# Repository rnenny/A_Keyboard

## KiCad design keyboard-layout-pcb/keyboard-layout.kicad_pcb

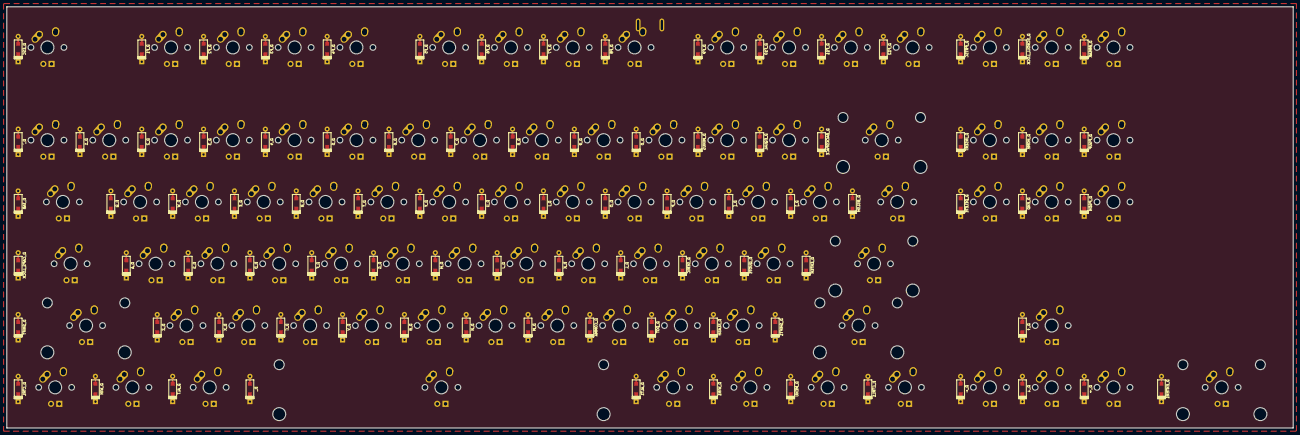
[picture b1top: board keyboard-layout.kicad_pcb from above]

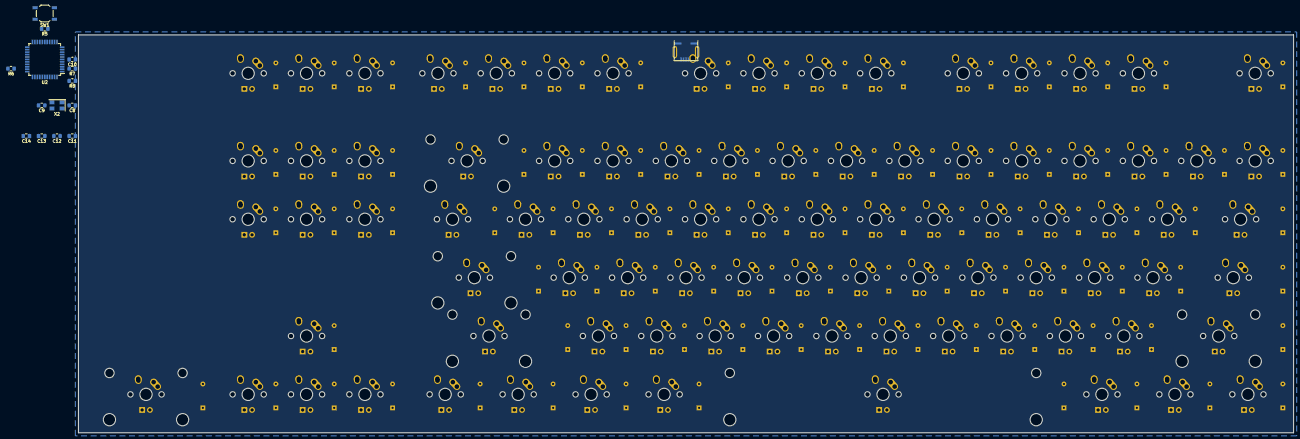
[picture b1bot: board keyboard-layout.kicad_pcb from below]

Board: 2 copper layers, 396.5 x 129.8 mm, 191 parts (15 on the bottom side), 116 nets, no tracks yet.

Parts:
C8, C9, C10, C11, C12, C13, C14: 22pF; C_0805_2012Metric_Pad1.15x1.40mm_HandSolder
D_, D_0, D_1, D_2, D_3, D_4, D_5, D_6, D_7, D_8, D_9: D; D_SOD123_axial
D_A: D; D_SOD123_axial
D_ALT, D_ALT1: D; D_SOD123_axial
D_B: D; D_SOD123_axial
D_BACKSPACE: D; D_SOD123_axial
D_BREAK: D; D_SOD123_axial
D_BSLSH: D; D_SOD123_axial
D_C: D; D_SOD123_axial
D_CAPS_LOCK: D; D_SOD123_axial
D_COMMA: D; D_SOD123_axial
D_CTRL, D_CTRL1: D; D_SOD123_axial
D_D: D; D_SOD123_axial
D_DELETE: D; D_SOD123_axial
D_DOT: D; D_SOD123_axial
D_E: D; D_SOD123_axial
D_END: D; D_SOD123_axial
D_ENTER, D_ENTER1: D; D_SOD123_axial
D_EQUAL: D; D_SOD123_axial
D_ESC: D; D_SOD123_axial
D_F, D_F1, D_F2, D_F3, D_F4, D_F5, D_F6, D_F7, D_F8, D_F9, D_F10, D_F11, D_F12: D; D_SOD123_axial
D_G: D; D_SOD123_axial
D_H: D; D_SOD123_axial
D_HOME: D; D_SOD123_axial
D_I: D; D_SOD123_axial
D_INSERT: D; D_SOD123_axial
D_J: D; D_SOD123_axial
D_K: D; D_SOD123_axial
D_L: D; D_SOD123_axial
D_M: D; D_SOD123_axial
D_MENU: D; D_SOD123_axial
D_MINUS: D; D_SOD123_axial
D_N: D; D_SOD123_axial
D_O: D; D_SOD123_axial
D_P: D; D_SOD123_axial
D_PGDN: D; D_SOD123_axial
D_PGUP: D; D_SOD123_axial
D_PRTSC: D; D_SOD123_axial
D_Q: D; D_SOD123_axial
D_QUOTE: D; D_SOD123_axial
D_R: D; D_SOD123_axial
D_S: D; D_SOD123_axial
D_SCROLL_LOCK: D; D_SOD123_axial
D_SEMIC: D; D_SOD123_axial
D_SHIFT, D_SHIFT1: D; D_SOD123_axial
D_SLASH: D; D_SOD123_axial
D_T: D; D_SOD123_axial
D_TAB: D; D_SOD123_axial
D_U: D; D_SOD123_axial
D_V: D; D_SOD123_axial
D_W: D; D_SOD123_axial
D_WIN, D_WIN1: D; D_SOD123_axial
D_X: D; D_SOD123_axial
D_Y: D; D_SOD123_axial
D_Z: D; D_SOD123_axial
D_[: D; D_SOD123_axial
D_]: D; D_SOD123_axial
D_`: D; D_SOD123_axial
D_←: D; D_SOD123_axial
D_↑: D; D_SOD123_axial
D_→: D; D_SOD123_axial
D_↓: D; D_SOD123_axial
K_: KEYSW; MX-6.25U-NoLED
K_0, K_1, K_2, K_3, K_4, K_5, K_6, K_7, K_8, K_9: KEYSW; MX-1U-NoLED
K_A: KEYSW; MX-1U-NoLED
K_ALT, K_ALT1: KEYSW; MX-1.25U-NoLED
K_B: KEYSW; MX-1U-NoLED
K_BACKSPACE: KEYSW; MX-2U-NoLED
K_BREAK: KEYSW; MX-1U-NoLED
K_BSLSH: KEYSW; MX-1.5U-NoLED
K_C: KEYSW; MX-1U-NoLED
K_CAPS_LOCK: KEYSW; MX-1.75U-NoLED
K_COMMA: KEYSW; MX-1U-NoLED
K_CTRL, K_CTRL1: KEYSW; MX-1.25U-NoLED
K_D: KEYSW; MX-1U-NoLED
K_DELETE: KEYSW; MX-1U-NoLED
K_DOT: KEYSW; MX-1U-NoLED
K_E: KEYSW; MX-1U-NoLED
K_END: KEYSW; MX-1U-NoLED
K_ENTER: KEYSW; MX-2.25U-NoLED
K_ENTER1: KEYSW; MX-2U-NoLED
K_EQUAL: KEYSW; MX-1U-NoLED
K_ESC: KEYSW; MX-1U-NoLED
K_F, K_F1, K_F2, K_F3, K_F4, K_F5, K_F6, K_F7, K_F8, K_F9, K_F10, K_F11, K_F12: KEYSW; MX-1U-NoLED
K_G: KEYSW; MX-1U-NoLED
K_H: KEYSW; MX-1U-NoLED
K_HOME: KEYSW; MX-1U-NoLED
K_I: KEYSW; MX-1U-NoLED
K_INSERT: KEYSW; MX-1U-NoLED
K_J: KEYSW; MX-1U-NoLED
K_K: KEYSW; MX-1U-NoLED
K_L: KEYSW; MX-1U-NoLED
K_M: KEYSW; MX-1U-NoLED
K_MENU: KEYSW; MX-1.25U-NoLED
K_MINUS: KEYSW; MX-1U-NoLED
K_N: KEYSW; MX-1U-NoLED
K_O: KEYSW; MX-1U-NoLED
K_P: KEYSW; MX-1U-NoLED
K_PGDN: KEYSW; MX-1U-NoLED
K_PGUP: KEYSW; MX-1U-NoLED
K_PRTSC: KEYSW; MX-1U-NoLED
K_Q: KEYSW; MX-1U-NoLED
K_QUOTE: KEYSW; MX-1U-NoLED
K_R: KEYSW; MX-1U-NoLED
K_S: KEYSW; MX-1U-NoLED
K_SCROLL_LOCK: KEYSW; MX-1U-NoLED
K_SEMIC: KEYSW; MX-1U-NoLED
K_SHIFT: KEYSW; MX-2.25U-NoLED
K_SHIFT1: KEYSW; MX-2.75U-NoLED
K_SLASH: KEYSW; MX-1U-NoLED
K_T: KEYSW; MX-1U-NoLED
K_TAB: KEYSW; MX-1.5U-NoLED
K_U: KEYSW; MX-1U-NoLED
K_V: KEYSW; MX-1U-NoLED
K_W: KEYSW; MX-1U-NoLED
K_WIN, K_WIN1: KEYSW; MX-1.25U-NoLED
K_X: KEYSW; MX-1U-NoLED
K_Y: KEYSW; MX-1U-NoLED
K_Z: KEYSW; MX-1U-NoLED
K_[: KEYSW; MX-1U-NoLED
K_]: KEYSW; MX-1U-NoLED
K_`: KEYSW; MX-1U-NoLED
K_←: KEYSW; MX-1U-NoLED
K_↑: KEYSW; MX-1U-NoLED
K_→: KEYSW; MX-1U-NoLED
K_↓: KEYSW; MX-1U-NoLED
R5, R6: 10k; R_0805_2012Metric_Pad1.15x1.40mm_HandSolder
R7, R8: 22u; R_0805_2012Metric_Pad1.15x1.40mm_HandSolder
SW1: SW_PUSH; SW_SPST_TL3342
U2: ATMEGA32U4; TQFP-44_10x10mm_P0.8mm
USB2: USB_mini_micro_B; USB_miniB_hirose_5S8
X2: XTAL_GND; Crystal_SMD_5032-4Pin_5.0x3.2mm

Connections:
/col0: D_CAPS_LOCK.1, D_CTRL.1, D_ESC.1, D_SHIFT.1, D_TAB.1, D_`.1, U2.32
/col1: D_1.1, D_A.1, D_F1.1, D_Q.1, D_WIN.1, D_Z.1, U2.31
/col2: D_2.1, D_ALT.1, D_F2.1, D_S.1, D_W.1, D_X.1, U2.12
/col3: D_.1, D_3.1, D_C.1, D_D.1, D_E.1, D_F3.1, U2.30
/col4: D_4.1, D_ALT1.1, D_F.1, D_F4.1, D_R.1, D_V.1, U2.29
/col5: D_5.1, D_B.1, D_F5.1, D_G.1, D_T.1, D_WIN1.1, U2.28
/col6: D_6.1, D_F6.1, D_H.1, D_MENU.1, D_N.1, D_Y.1, U2.11
/col7: D_7.1, D_CTRL1.1, D_F7.1, D_J.1, D_M.1, D_U.1, U2.10
/col8: D_8.1, D_COMMA.1, D_F8.1, D_I.1, D_K.1, D_←.1, U2.9
/col9: D_9.1, D_DOT.1, D_F9.1, D_L.1, D_O.1, D_↓.1, U2.8
/col10: D_0.1, D_F10.1, D_P.1, D_SEMIC.1, D_SLASH.1, D_→.1, U2.37
/col11: D_ENTER1.1, D_F11.1, D_MINUS.1, D_QUOTE.1, D_SHIFT1.1, D_[.1, U2.38
/col12: D_ENTER.1, D_EQUAL.1, D_F12.1, D_].1, D_↑.1, U2.39
/col13: D_BACKSPACE.1, D_BSLSH.1, D_PRTSC.1, U2.40
/col14: D_DELETE.1, D_INSERT.1, D_SCROLL_LOCK.1, U2.41
/col15: D_BREAK.1, D_END.1, D_HOME.1
/col16: D_PGDN.1, D_PGUP.1
GND: C8.2, C9.2, C10.2, C11.2, C12.2, C13.2, C14.2, R6.2, SW1.1, U2.5, U2.15, U2.23, USB2.5, USB2.6, X2.3
unnamed: C8.1, U2.16
unnamed: C9.1, U2.17
unnamed: C10.1, U2.6
unnamed: D_0.2, K_0.2
unnamed: D_1.2, K_1.2
unnamed: D_2.2, K_2.2
unnamed: D_3.2, K_3.2
unnamed: D_4.2, K_4.2
unnamed: D_5.2, K_5.2
unnamed: D_6.2, K_6.2
unnamed: D_7.2, K_7.2
unnamed: D_8.2, K_8.2
unnamed: D_9.2, K_9.2
unnamed: D_.2, K_.2
unnamed: D_A.2, K_A.2
unnamed: D_ALT1.2, K_ALT1.2
unnamed: D_ALT.2, K_ALT.2
unnamed: D_B.2, K_B.2
unnamed: D_BACKSPACE.2, K_BACKSPACE.2
unnamed: D_BREAK.2, K_BREAK.2
unnamed: D_BSLSH.2, K_BSLSH.2
unnamed: D_C.2, K_C.2
unnamed: D_CAPS_LOCK.2, K_CAPS_LOCK.2
unnamed: D_COMMA.2, K_COMMA.2
unnamed: D_CTRL1.2, K_CTRL1.2
unnamed: D_CTRL.2, K_CTRL.2
unnamed: D_D.2, K_D.2
unnamed: D_DELETE.2, K_DELETE.2
unnamed: D_DOT.2, K_DOT.2
unnamed: D_E.2, K_E.2
unnamed: D_END.2, K_END.2
unnamed: D_ENTER1.2, K_ENTER1.2
unnamed: D_ENTER.2, K_ENTER.2
unnamed: D_EQUAL.2, K_EQUAL.2
unnamed: D_ESC.2, K_ESC.2
unnamed: D_F1.2, K_F1.2
unnamed: D_F2.2, K_F2.2
unnamed: D_F3.2, K_F3.2
unnamed: D_F4.2, K_F4.2
unnamed: D_F5.2, K_F5.2
unnamed: D_F6.2, K_F6.2
unnamed: D_F7.2, K_F7.2
unnamed: D_F8.2, K_F8.2
unnamed: D_F9.2, K_F9.2
unnamed: D_F10.2, K_F10.2
unnamed: D_F11.2, K_F11.2
unnamed: D_F12.2, K_F12.2
unnamed: D_F.2, K_F.2
unnamed: D_G.2, K_G.2
unnamed: D_H.2, K_H.2
unnamed: D_HOME.2, K_HOME.2
unnamed: D_I.2, K_I.2
unnamed: D_INSERT.2, K_INSERT.2
unnamed: D_J.2, K_J.2
unnamed: D_K.2, K_K.2
unnamed: D_L.2, K_L.2
unnamed: D_M.2, K_M.2
unnamed: D_MENU.2, K_MENU.2
unnamed: D_MINUS.2, K_MINUS.2
unnamed: D_N.2, K_N.2
unnamed: D_O.2, K_O.2
unnamed: D_P.2, K_P.2
unnamed: D_PGDN.2, K_PGDN.2
unnamed: D_PGUP.2, K_PGUP.2
unnamed: D_PRTSC.2, K_PRTSC.2
unnamed: D_Q.2, K_Q.2
unnamed: D_QUOTE.2, K_QUOTE.2
unnamed: D_R.2, K_R.2
unnamed: D_S.2, K_S.2
unnamed: D_SCROLL_LOCK.2, K_SCROLL_LOCK.2
unnamed: D_SEMIC.2, K_SEMIC.2
unnamed: D_SHIFT1.2, K_SHIFT1.2
unnamed: D_SHIFT.2, K_SHIFT.2
unnamed: D_SLASH.2, K_SLASH.2
unnamed: D_T.2, K_T.2
unnamed: D_TAB.2, K_TAB.2
unnamed: D_U.2, K_U.2
unnamed: D_V.2, K_V.2
unnamed: D_W.2, K_W.2
unnamed: D_WIN1.2, K_WIN1.2
unnamed: D_WIN.2, K_WIN.2
unnamed: D_X.2, K_X.2
unnamed: D_Y.2, K_Y.2
unnamed: D_Z.2, K_Z.2
unnamed: D_[.2, K_[.2
unnamed: D_].2, K_].2
unnamed: D_`.2, K_`.2
unnamed: D_←.2, K_←.2
unnamed: D_↑.2, K_↑.2
unnamed: D_→.2, K_→.2
unnamed: D_↓.2, K_↓.2
unnamed: R5.1, SW1.2, U2.13
unnamed: R6.1, U2.33
unnamed: R7.1, U2.3
unnamed: R8.1, U2.4
unnamed: R7.2, USB2.2
unnamed: R8.2, USB2.3
VCC: C11.1, C12.1, C13.1, C14.1, R5.2, U2.2, U2.14, U2.24, USB2.1

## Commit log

2020-05-12 Progress
    Add Libraries
    Add Feather32u4 symbol
2020-05-14 Remove old files from repo
